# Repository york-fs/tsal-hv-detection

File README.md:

# TSAL HV Detection Board

Detects if >60 V is present between TS+ and TS- and outputs a 5 V signal (inverted logic for SCS rule compliance).

## Cloning

A recursive clone must be used to download the `kicad-library` repository:

    git clone --recursive https://github.com/york-fs/tsal-hv-detection.git

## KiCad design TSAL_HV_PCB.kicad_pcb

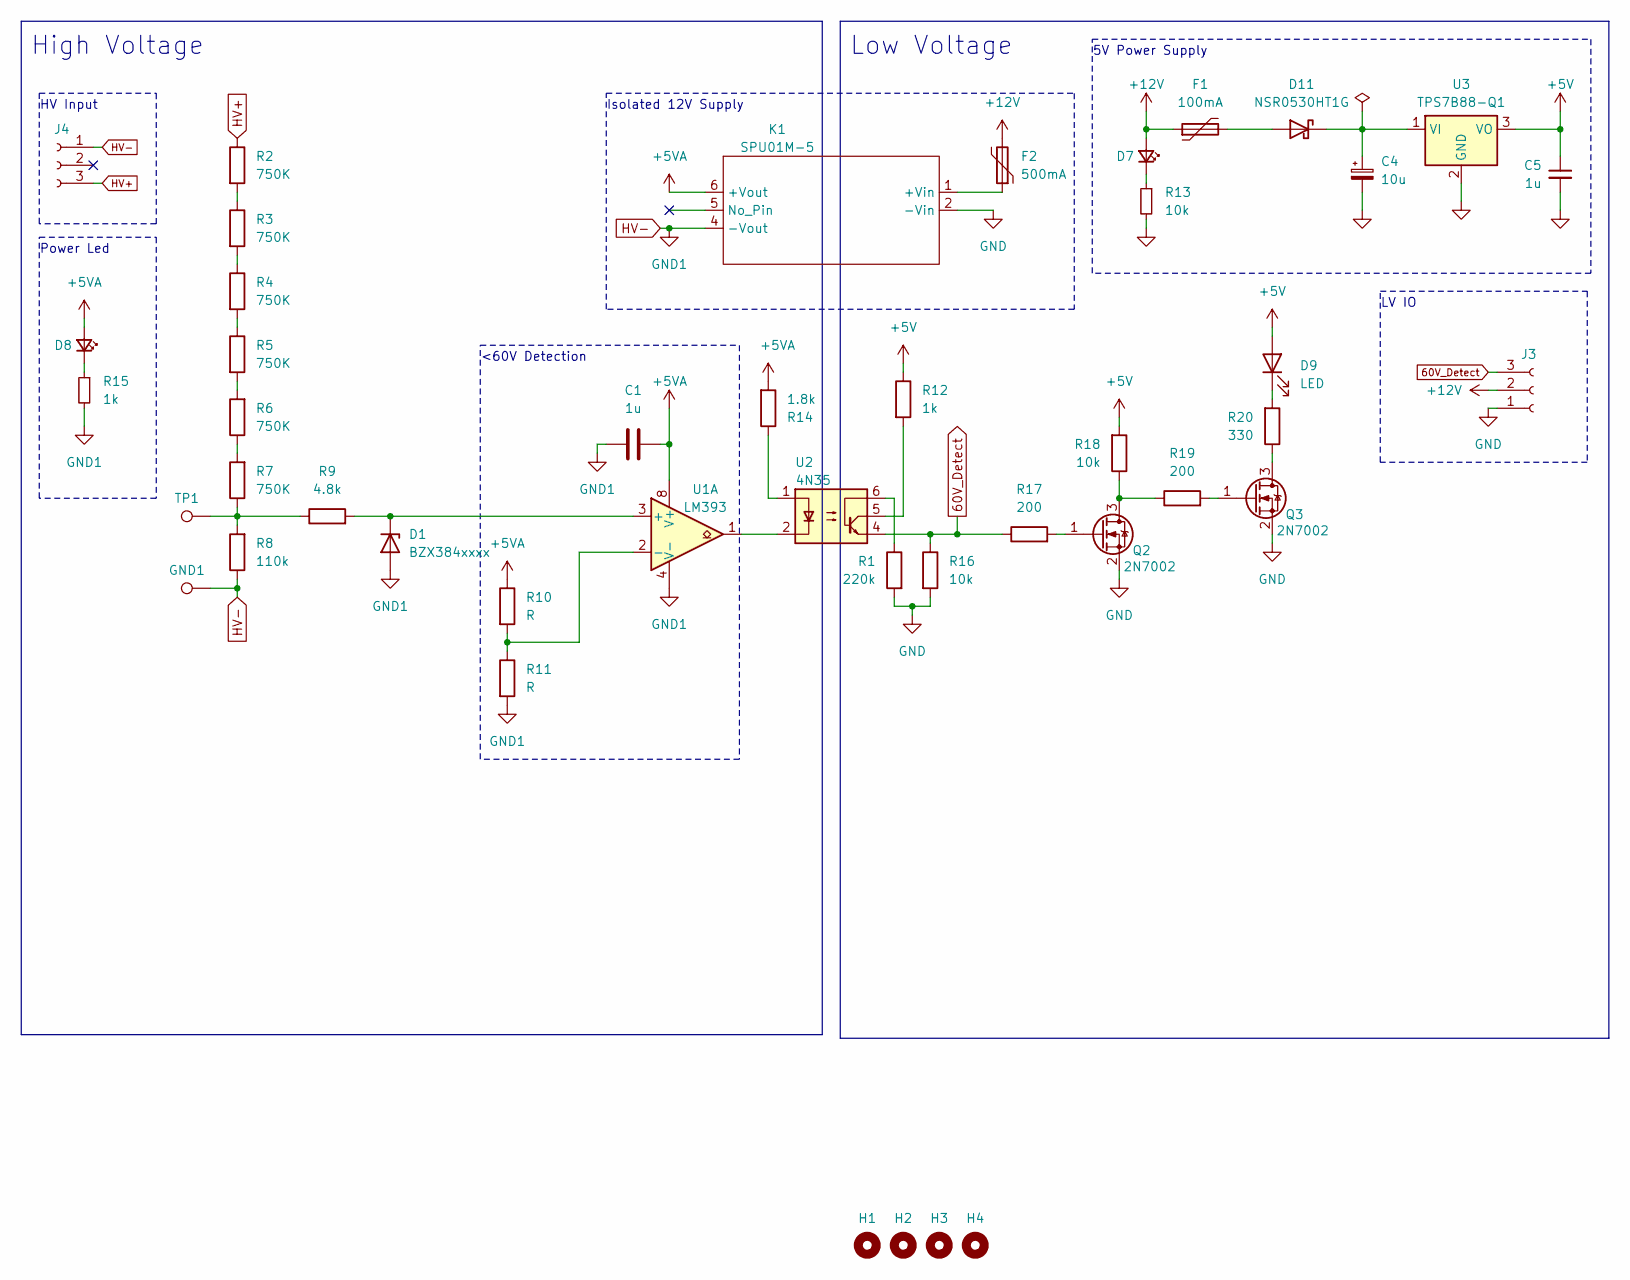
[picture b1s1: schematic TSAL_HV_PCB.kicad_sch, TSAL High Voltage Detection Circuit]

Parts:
C1, C5: 1u; C_0603_1608Metric
C4: 10u; CP_Elec_6.3x5.4
D1: BZX384xxxx; D_SOD-323
D7, D8: LED_Small; LED_0603_1608Metric
D9: LED; LED_0603_1608Metric
D11: NSR0530HT1G; D_SOD-323
F1: 100mA; R_0805_2012Metric
F2: 500mA; R_0805_2012Metric
GND1: TestPoint; TestPoint_Keystone_5000-5004_Miniature
H1, H2, H3, H4: MountingHole; MountingHole_3.2mm_M3
J3, J4: Conn_01x03_Socket; MolexMicrofitPlus1x3
K1: SPU01M-5
Q2, Q3: 2N7002; SOT-23
R1: 220k; R_0603_1608Metric
R2, R3, R4, R5, R6, R7: 750K; R_1206_3216Metric
R8: 110k; R_1206_3216Metric
R9: 4.8k; R_0603_1608Metric
R10, R11: R; R_0603_1608Metric
R12, R15: 1k; R_0603_1608Metric
R13, R16, R18: 10k; R_0603_1608Metric
R14: 1.8k; R_0603_1608Metric
R17, R19: 200; R_0603_1608Metric
R20: 330; R_0603_1608Metric
TP1: TestPoint; TestPoint_Keystone_5000-5004_Miniature
U1: LM393; SOIC-8_3.9x4.9mm_P1.27mm
U2: 4N35; DIP-6_W7.62mm
U3: TPS7B88-Q1; TO-252-2

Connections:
60V_Detect: J3.3, R16.1, R17.1, U2.4
+5V: C5.1, D9.2 (A), R12.1, R18.2, U3.3 (VO)
+5VA: C1.2, D8.2 (A), K1.6 (+Vout), R10.1, R14.2, U1.8 (V+)
+12V: D7.2 (A), F1.1, F2.2, J3.2
GND: C4.2, C5.2, J3.1, K1.2 (-Vin), Q2.2 (S), Q3.2 (S), R1.2, R13.2, R16.2, U3.2 (GND)
HV+: J4.3, R2.1
HV-: C1.1, D1.2 (A), GND1.1, J4.1, K1.4 (-Vout), R8.1, R11.2, R15.2, U1.4 (V-)
unnamed: D1.1 (K), R9.2, U1.3 (+)
unnamed: D7.1 (K), R13.1
unnamed: D8.1 (K), R15.1
unnamed: D9.1 (K), R20.2
unnamed: D11.2 (A), F1.2
unnamed: C4.1, D11.1 (K), U3.1 (VI)
unnamed: F2.1, K1.1 (+Vin)
unnamed: Q2.3 (D), R18.1, R19.1
unnamed: Q2.1 (G), R17.2
unnamed: Q3.3 (D), R20.1
unnamed: Q3.1 (G), R19.2
unnamed: R1.1, U2.6
unnamed: R2.2, R3.1
unnamed: R3.2, R4.1
unnamed: R4.2, R5.1
unnamed: R5.2, R6.2
unnamed: R6.1, R7.2
unnamed: R7.1, R8.2, R9.1, TP1.1
unnamed: R12.2, U2.5
unnamed: R14.1, U2.1
unnamed: U1.1, U2.2
unnamed: R10.2, R11.1, U1.2 (-)

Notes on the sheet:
Isolated 12V Supply
LV IO
High Voltage
HV Input
<60V Detection
5V Power Supply
Power Led
Low Voltage

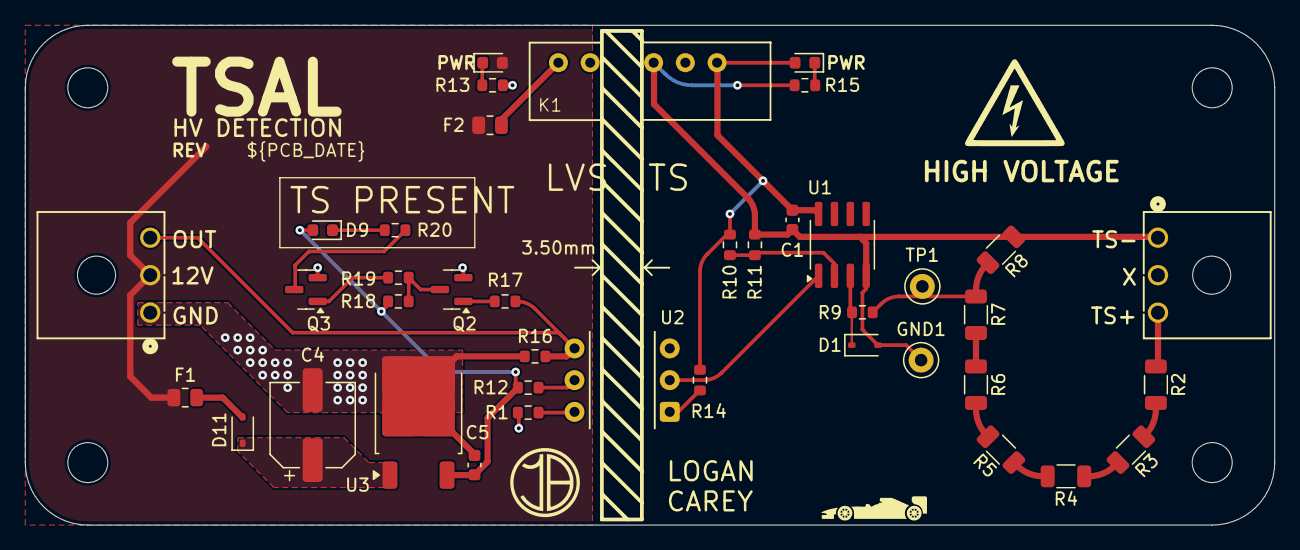
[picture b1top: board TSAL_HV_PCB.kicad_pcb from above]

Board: 2 copper layers, 100.0 x 40.0 mm, 44 parts (0 on the bottom side), 29 nets.

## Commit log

2025-11-07 *: Add series resistor and pull-down to optocoupler BJT
    The series resistor protects against shorts on the output and the base
    pull-down helps with noise immunity.
2025-11-22 meta: Update gitignore
2025-11-22 meta: Set LF line endings explicitly
2025-11-23 ci: Add kicad workflow
2025-11-23 meta: Add some badges to the README
